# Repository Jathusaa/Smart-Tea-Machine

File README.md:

# Smart Tea Machine

This project features a Smart Tea Machine designed to automate the tea-making process. The machine includes various advanced features to enhance user experience:

## Features

- **Automatic Water Dispensing:** Dispenses the right amount of water for each cup of tea.
- **Tea Bag Dipping:** Dips the tea bag into the water to ensure optimal brewing.
- **Sugar Dispensing:** Automatically dispenses sugar according to user preferences.
- **Temperature Check:** Monitors the water temperature to ensure the perfect brewing conditions.
- **User Card System:** Utilizes RFID technology to recognize user preferences and customize the tea-making process.
- **User-Friendly Interface:** Designed for easy operation, featuring clear instructions and feedback.
- **Sound Alerts:** Equipped with a buzzer to alert the user when the tea is ready.

## Project Files

This repository includes the following files:

- **Arduino Code:** The main code for controlling the Smart Tea Machine.
- **PCB Files:** Design files for the printed circuit board (PCB) used in the machine.
- **Project Report:** A comprehensive PDF report explaining the design, functionality, and components of the Smart Tea Machine.

## Contributors

Thanks to the following team members for their contributions to this project:

- **[Jathusaa Indrakumaran](https://github.com/yourusername)** 
- **[Anisa Matan](https://github.com/Anisa-M1)** 
- **[Vishwa Prajapati](https://github.com/vishwapraja)**

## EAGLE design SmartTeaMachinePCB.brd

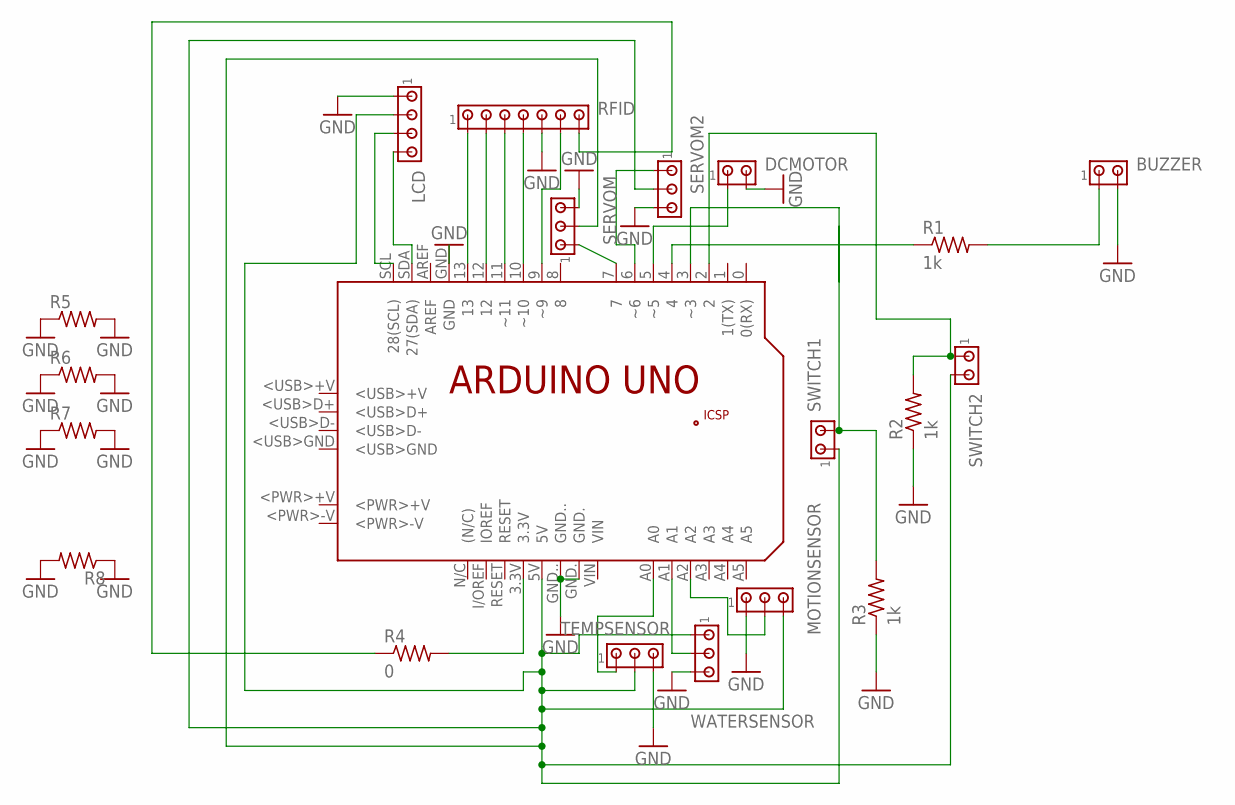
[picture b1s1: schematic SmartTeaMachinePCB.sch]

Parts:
BUZZER: MTA02-100; 10X02MTA
DCMOTOR: MTA02-100; 10X02MTA
LCD: MTA04-100; 10X04MTA
MOTIONSENSOR: MTA03-100; 10X03MTA
PCB1: ARDUINO_UNO
R1, R2, R3: 1k; 0207/10
R4: 0; 0207/10
R5, R6, R7, R8: R-US_0207/10; 0207/10
RFID: MTA07-100; 10X07MTA
SERVOM, SERVOM2: MTA03-100; 10X03MTA
SWITCH1, SWITCH2: MTA02-100; 10X02MTA
TEMPSENSOR: MTA03-100; 10X03MTA
WATERSENSOR: MTA03-100; 10X03MTA

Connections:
GND: BUZZER.2, DCMOTOR.2, LCD.1, MOTIONSENSOR.1, PCB1.GND, PCB1.GND., PCB1.GND.., R2.1, R3.1, R5.1, R5.2, R6.1, R6.2, R7.1, R7.2, R8.1, R8.2, RFID.5, SERVOM.3, SERVOM2.3, TEMPSENSOR.3, WATERSENSOR.3
unnamed: PCB1.7, SERVOM.1
unnamed: PCB1.6 (~6), SERVOM2.1
unnamed: PCB1.A1, WATERSENSOR.2
unnamed: PCB1.A0, TEMPSENSOR.1
unnamed: LCD.2, MOTIONSENSOR.3, PCB1.5V, SERVOM.2, SERVOM2.2, SWITCH1.1, SWITCH2.2, TEMPSENSOR.2, WATERSENSOR.1
unnamed: LCD.3, PCB1.SCL (28(SCL))
unnamed: LCD.4, PCB1.SDA (27(SDA))
unnamed: PCB1.13, RFID.1
unnamed: PCB1.12, RFID.2
unnamed: MOTIONSENSOR.2, PCB1.A2
unnamed: PCB1.11 (~11), RFID.3
unnamed: PCB1.10 (~10), RFID.4
unnamed: PCB1.9 (~9), RFID.6
unnamed: R4.1, RFID.7
unnamed: DCMOTOR.1, PCB1.5 (~5)
unnamed: PCB1.4, R1.1
unnamed: BUZZER.1, R1.2
unnamed: PCB1.2, R2.2, SWITCH2.1
unnamed: PCB1.3.3V, R4.2
unnamed: PCB1.3 (~3), R3.2, SWITCH1.2

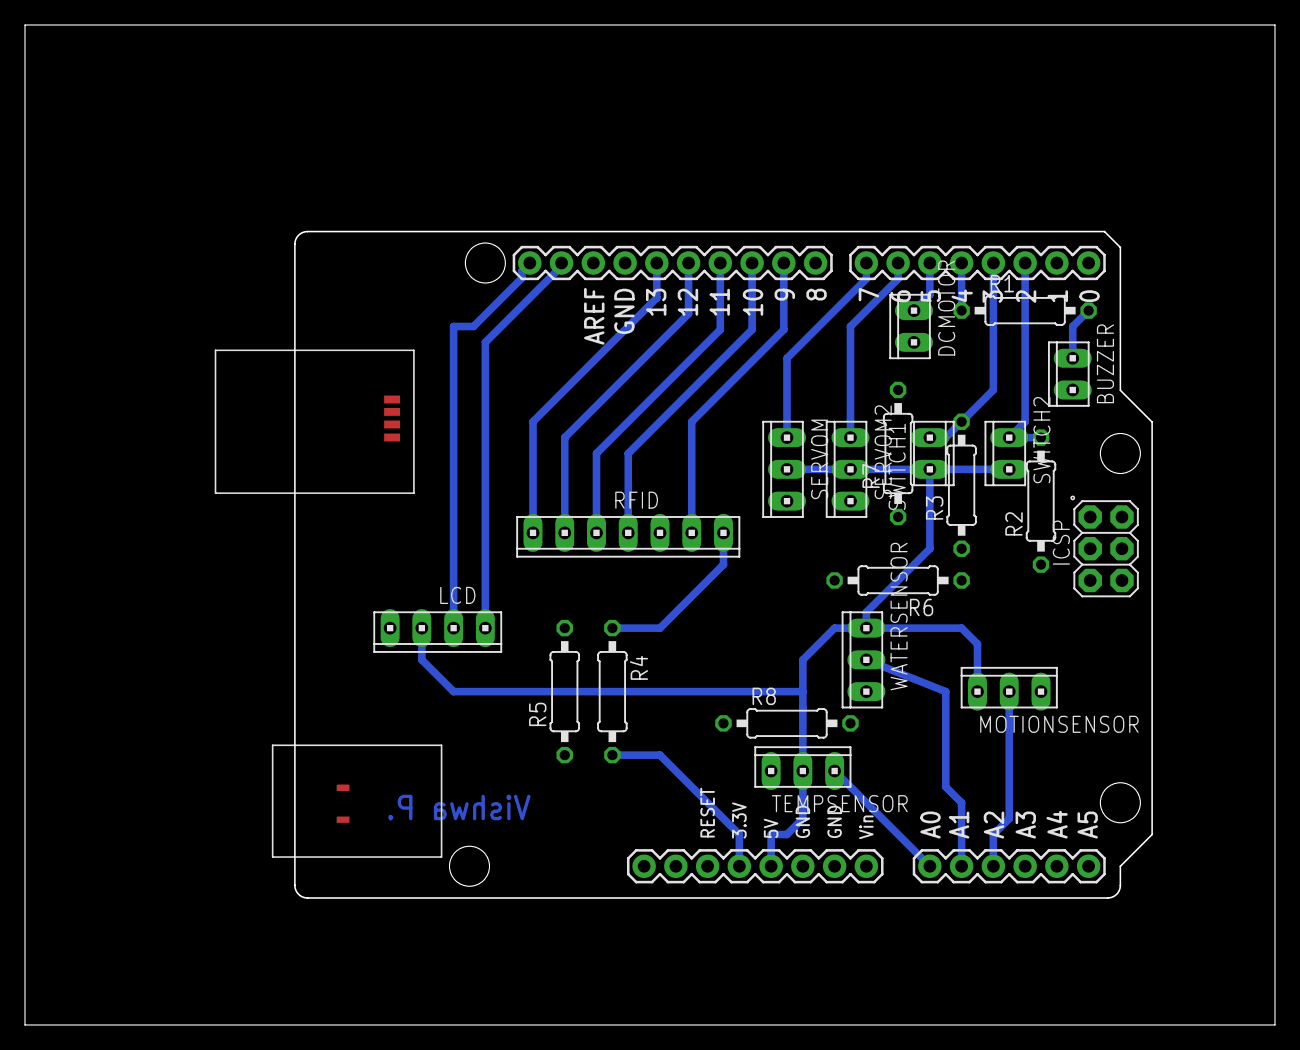
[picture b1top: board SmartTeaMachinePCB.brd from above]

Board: 2 copper layers, 99.9 x 79.9 mm, 20 parts (0 on the bottom side), 21 nets.
